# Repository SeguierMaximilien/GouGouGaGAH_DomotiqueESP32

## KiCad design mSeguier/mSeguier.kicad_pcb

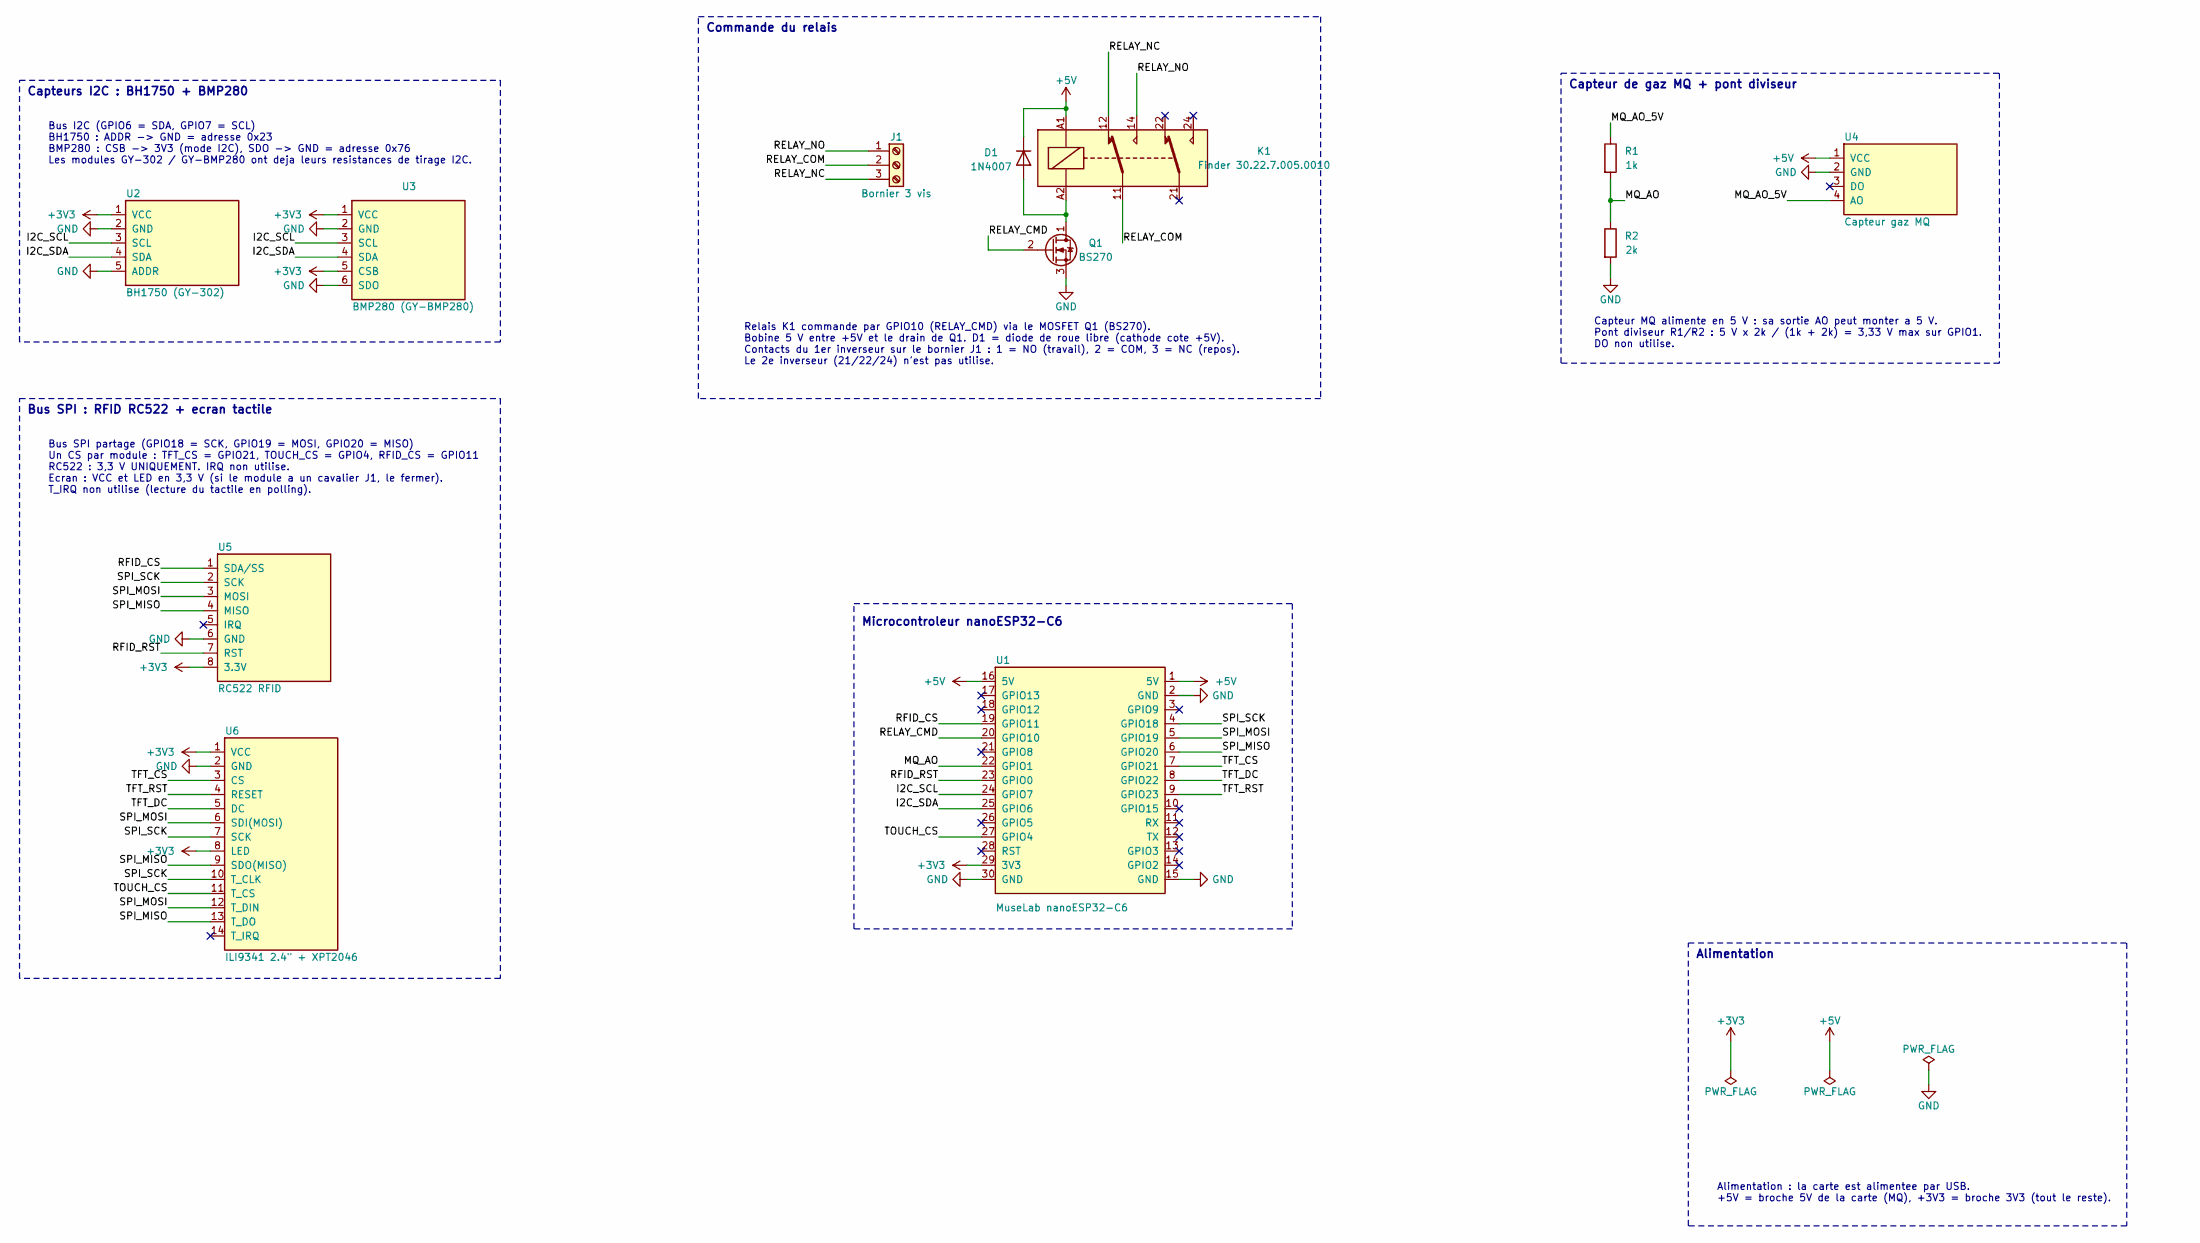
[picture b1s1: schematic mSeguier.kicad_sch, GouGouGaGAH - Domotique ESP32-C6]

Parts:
D1: 1N4007; D_DO-41_SOD81_P10.16mm_Horizontal
J1: Bornier 3 vis; TerminalBlock_Phoenix_MKDS-1,5-3_1x03_P5.00mm_Horizontal
K1: Finder 30.22.7.005.0010; Relay_DPDT_Finder_30.22
Q1: BS270; TO-92_Inline_Wide
R1: 1k; R_Axial_DIN0207_L6.3mm_D2.5mm_P10.16mm_Horizontal
R2: 2k; R_Axial_DIN0207_L6.3mm_D2.5mm_P10.16mm_Horizontal
U1: MuseLab nanoESP32-C6; MuseLab_nanoESP32-C6
U2: BH1750 (GY-302); BH1750_GY-302
U3: BMP280 (GY-BMP280); BMP280_GY-BMP280-3.3
U4: Capteur gaz MQ; MQ_Gas_Sensor_Module_FlyingFish
U5: RC522 RFID; RFID_RC522_Module
U6: ILI9341 2.4" + XPT2046; TFT_2.4in_SPI_ILI9341_MSP2402

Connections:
+3V3: U1.29 (3V3), U2.1 (VCC), U3.1 (VCC), U3.5 (CSB), U5.8 (3.3V), U6.1 (VCC), U6.8 (LED)
+5V: D1.1 (K), K1.A1, U1.1 (5V), U1.16 (5V), U4.1 (VCC)
/I2C_SCL: U1.24 (GPIO7), U2.3 (SCL), U3.3 (SCL)
/I2C_SDA: U1.25 (GPIO6), U2.4 (SDA), U3.4 (SDA)
/MQ_AO: R1.2, R2.1, U1.22 (GPIO1)
/MQ_AO_5V: R1.1, U4.4 (AO)
/RELAY_CMD: Q1.2 (G), U1.20 (GPIO10)
/RELAY_COM: J1.2, K1.11
/RELAY_NC: J1.3, K1.12
/RELAY_NO: J1.1, K1.14
/RFID_CS: U1.19 (GPIO11), U5.1 (SDA/SS)
/RFID_RST: U1.23 (GPIO0), U5.7 (RST)
/SPI_MISO: U1.6 (GPIO20), U5.4 (MISO), U6.9 (SDO(MISO)), U6.13 (T_DO)
/SPI_MOSI: U1.5 (GPIO19), U5.3 (MOSI), U6.6 (SDI(MOSI)), U6.12 (T_DIN)
/SPI_SCK: U1.4 (GPIO18), U5.2 (SCK), U6.7 (SCK), U6.10 (T_CLK)
/TFT_CS: U1.7 (GPIO21), U6.3 (CS)
/TFT_DC: U1.8 (GPIO22), U6.5 (DC)
/TFT_RST: U1.9 (GPIO23), U6.4 (RESET)
/TOUCH_CS: U1.27 (GPIO4), U6.11 (T_CS)
GND: Q1.3 (S), R2.2, U1.2 (GND), U1.15 (GND), U1.30 (GND), U2.2 (GND), U2.5 (ADDR), U3.2 (GND), U3.6 (SDO), U4.2 (GND), U5.6 (GND), U6.2 (GND)
unnamed: D1.2 (A), K1.A2, Q1.1 (D)

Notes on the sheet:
Capteur de gaz MQ + pont diviseur
Bus SPI : RFID RC522 + ecran tactile
Bus SPI partage (GPIO18 = SCK, GPIO19 = MOSI, GPIO20 = MISO) Un CS par module : TFT_CS = GPIO21, TOUCH_CS = GPIO4, RFID_CS = GPIO11 RC522 : 3,3 V UNIQUEMENT. IRQ non utilise. Ecran : VCC et LED en 3,3 V (si le module a un cavalier J1, le fermer). T_IRQ non utilise (lecture du tactile en polling).
Capteurs I2C : BH1750 + BMP280
Commande du relais
Alimentation
Relais K1 commande par GPIO10 (RELAY_CMD) via le MOSFET Q1 (BS270). Bobine 5 V entre +5V et le drain de Q1. D1 = diode de roue libre (cathode cote +5V). Contacts du 1er inverseur sur le bornier J1 : 1 = NO (travail), 2 = COM, 3 = NC (repos). Le 2e inverseur (21/22/24) n'est pas utilise.
Alimentation : la carte est alimentee par USB. +5V = broche 5V de la carte (MQ), +3V3 = broche 3V3 (tout le reste).
Microcontroleur nanoESP32-C6
Capteur MQ alimente en 5 V : sa sortie AO peut monter a 5 V. Pont diviseur R1/R2 : 5 V x 2k / (1k + 2k) = 3,33 V max sur GPIO1. DO non utilise.
Bus I2C (GPIO6 = SDA, GPIO7 = SCL) BH1750 : ADDR -> GND = adresse 0x23 BMP280 : CSB -> 3V3 (mode I2C), SDO -> GND = adresse 0x76 Les modules GY-302 / GY-BMP280 ont deja leurs resistances de tirage I2C.

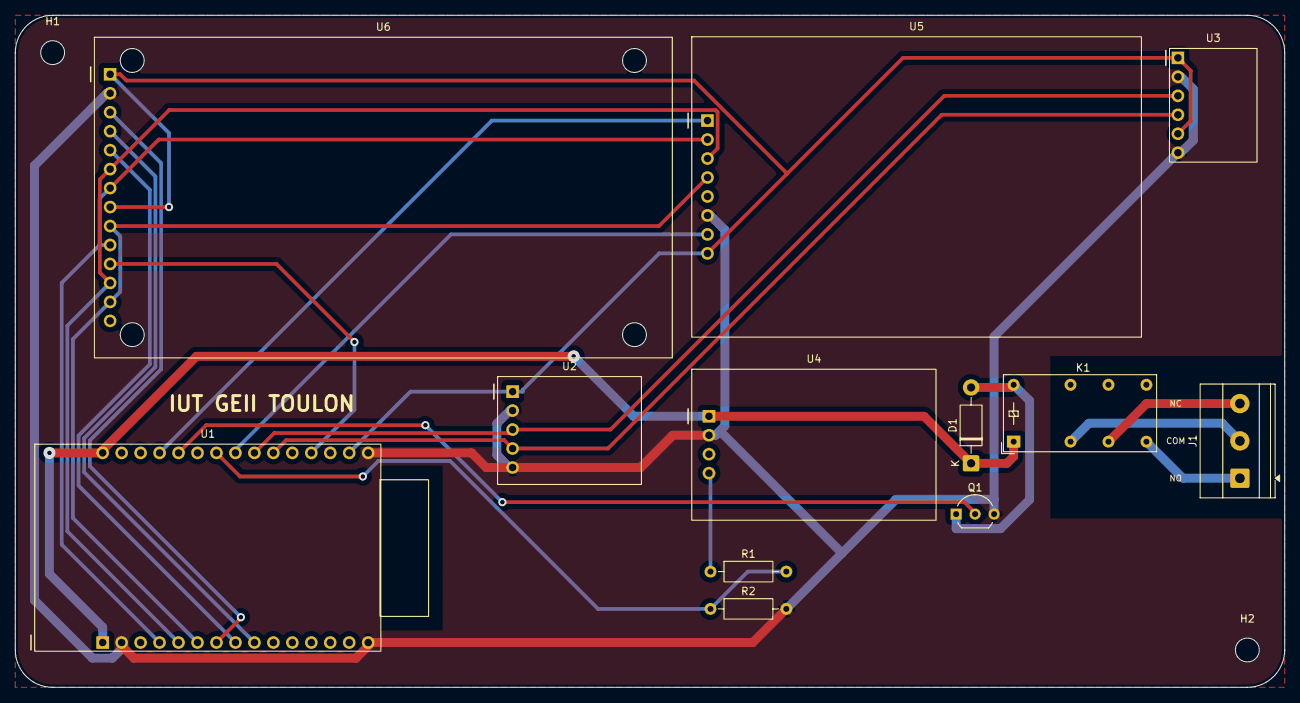
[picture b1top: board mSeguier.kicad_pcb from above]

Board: 2 copper layers, 170.0 x 90.0 mm, 14 parts (0 on the bottom side), 21 nets.

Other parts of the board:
H1, H2: M3; MountingHole_3.2mm_M3

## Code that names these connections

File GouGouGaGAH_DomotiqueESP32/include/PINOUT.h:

#ifndef PINOUT_H
#define PINOUT_H

// ========================================================
// PINOUT - ESP32-C6-WROOM
// ========================================================

// ---- Bus I2C (BH1750 + BMP280) ----
#define I2C_SDA     6
#define I2C_SCL     7

// ---- Bus SPI partagé (TFT + Tactile + RC522) ----
#define SPI_SCK     18
#define SPI_MOSI    19
#define SPI_MISO    20

// ---- Ecran TFT ----
#define TFT_CS      21
#define TFT_DC      22
#define TFT_RST     23
// LED (retroeclairage) -> 3V3 direct, pas de GPIO

// ---- Tactile (partage SPI_SCK / SPI_MOSI / SPI_MISO) ----
#define TOUCH_CS    4

// ---- RFID RC522 (partage SPI_SCK / SPI_MOSI / SPI_MISO) ----
#define RFID_CS     11
#define RFID_RST    0

// ---- Capteur MQ (analogique) ----
#define MQ_AO       1

// ---- Relais (via transistor, actif a l'etat haut) ----
#define RELAIS_PIN  10

#endif // PINOUT_H

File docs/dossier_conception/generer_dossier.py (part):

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    e.append(fleche([(460, 388), (540, 388)], "SPI 18/19/20\nCS 21, 4, 11\nRST 23, 0", 500, 352, double=True))
    e.append(fleche([(790, 100), (880, 100)], "WiFi\nMQTT", 835, 84, double=True))
    e.append(fleche([(790, 225), (880, 225)], "HTTP\nTempo", 835, 209, double=True))
    e.append(fleche([(790, 365), (880, 365)], "RELAY_CMD\nGPIO10", 835, 349))
    e.append(fleche([(995, 430), (995, 470)], "contacts", 1003, 455, ancre="start"))
    e.append(fleche([(720, 455), (720, 595), (880, 595)], "PWM GPIO2", 770, 588))
    e.append(fleche([(995, 160), (995, 185)], "", double=True, couleur="#8a94a6"))
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<td>Mesure l'éclairement (lx), la température (°C) et la pression (hPa). Bus I2C partagé, adresses 0x23 et 0x76.</td></tr>
<tr><td>FP3 Détecter le gaz</td><td>Module MQ (U4), R1 1 kΩ, R2 2 kΩ</td>
<td>Donne une tension image de la concentration de gaz. Le pont diviseur ramène la sortie 0-5 V à 0-3,33 V
pour l'entrée analogique GPIO1.</td></tr>
<tr><td>FP4 Dialoguer avec l'habitant</td><td>Écran TFT 2,4" ILI9341 + XPT2046 (U6), RC522 (U5)</td>
<td>Affiche les mesures et les menus, reçoit les appuis tactiles, lit l'identifiant des badges. Bus SPI partagé,
un chip select par module.</td></tr>
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<td>Exécute le programme : contrôle d'accès, menus, mémoire des badges en NVS, MQTT vers Home Assistant,
lecture de la couleur Tempo, LED RGB, sortie PWM.</td></tr>
<tr><td>FP6 Commander la gâche</td><td>BS270 (Q1), D1, relais Finder 30.22.7.005 (K1), bornier J1</td>
<td>Le MOSFET commute la bobine 5 V du relais depuis GPIO10. D1 protège Q1 de la surtension à la coupure.
Les contacts NO/COM/NC sortent sur J1 vers la gâche.</td></tr>
</table>
<h2>Liaisons entre fonctions</h2>
<table>
<tr><th style="width:24%">Liaison</th><th style="width:22%">Nature</th><th>Signaux (GPIO de l'ESP32-C6)</th></tr>
<tr><td>FP2 → FP5</td><td>numérique, I2C</td><td>SDA = GPIO6, SCL = GPIO7</td></tr>
<tr><td>FP3 → FP5</td><td>analogique</td><td>MQ_AO divisé, 0 à 3,33 V sur GPIO1 (ADC 12 bits)</td></tr>
<tr><td>FP4 ↔ FP5</td><td>numérique, SPI</td><td>SCK = GPIO18, MOSI = GPIO19, MISO = GPIO20 ; TFT_CS = 21, TFT_DC = 22, TFT_RST = 23,
TOUCH_CS = 4, RFID_CS = 11, RFID_RST = 0</td></tr>
<tr><td>FP5 → FP6</td><td>logique TOR</td><td>RELAY_CMD = GPIO10, actif à l'état haut</td></tr>
<tr><td>FP5 → éclairage / VMC</td><td>PWM</td><td>GPIO2, rapport cyclique 0 à 100 %</td></tr>
<tr><td>FP5 → LED RGB</td><td>série WS2812</td><td>GPIO8 (LED intégrée à la carte)</td></tr>
<tr><td>FP5 ↔ Home Assistant</td><td>WiFi 2,4 GHz, MQTT</td><td>topics <code>gougougagah/…</code> (voir annexe B)</td></tr>
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<tr><td>R1, R2</td><td>Résistances 1 kΩ et 2 kΩ</td><td>FP3</td><td>5 V × 2k / (1k + 2k) = 3,33 V max</td></tr>
<tr><td>U5</td><td>Module RFID RC522</td><td>FP4</td><td>Alimenté en 3,3 V uniquement</td></tr>
<tr><td>U6</td><td>Écran TFT 2,4" ILI9341 + tactile XPT2046 (MSP2402)</td><td>FP4</td><td>Rétroéclairage sur 3V3</td></tr>
<tr><td>Q1</td><td>MOSFET canal N BS270</td><td>FP6</td><td>Commande de la bobine depuis GPIO10</td></tr>
<tr><td>D1</td><td>Diode 1N4004</td><td>FP6</td><td>Roue libre, cathode côté +5V</td></tr>
<tr><td>K1</td><td>Relais Finder 30.22.7.005.0010, 2RT, bobine 5 V</td><td>FP6</td><td>1er inverseur utilisé</td></tr>
<tr><td>J1</td><td>Bornier à vis 3 points</td><td>FP6</td><td>1 = NO, 2 = COM, 3 = NC</td></tr>
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<h2>Dimensionnement de la commande du relais</h2>
<p>La bobine 5 V du relais Finder 30.22 consomme environ 40 mA (résistance d'environ 125 Ω).
Une sortie de l'ESP32-C6 ne peut pas fournir ce courant sous 5 V : le MOSFET BS270 (V<sub>GS(th)</sub> inférieure à 2,5 V,
I<sub>D</sub> max 400 mA) est commandé directement en 3,3 V par GPIO10 et commute la bobine côté masse.
La diode D1 en parallèle sur la bobine écoule le courant de self à l'ouverture et protège Q1.</p>
"""

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        "module_tft": "Pilote de l'écran ILI9341 et du tactile XPT2046",
        "module_tempo": "Couleur Tempo EDF (tâche FreeRTOS) et LED RGB clignotante",
        "module_pwm": "Sortie PWM 0-100 % sur GPIO2",
        "module_relais": "Commande du relais K1 (GPIO10)",
        "module_rfid": "Lecture des badges RC522",
        "module_bh1750": "Capteur de lumière",
        "module_bmp280": "Capteur de température et de pression",
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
